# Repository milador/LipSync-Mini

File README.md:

# LipSync-Mini

Lipsync with updated electronics (Adafruit ItsyBitsy and RGB LED)

The LipSync is an assistive technology device developed by <a href="https://www.makersmakingchange.com/" download target="_blank">MakersMakingChange</a> (An initiative by the <a href="https://www.neilsquire.ca/" download target="_blank">Neil Squire Society</a>) which allows quadriplegics and other people with limited hand use the ability to use touchscreen mobile devices by manipulation of a mouth-operated joystick with integrated sip and puff controls. 

## Main LipSync github repository 

The LipSync Mini project is based on the <a href="https://github.com/makersmakingchange/LipSync" download target="_blank">LipSync</a>

## Changes Made

1. Dual color Led replaced by RGB addressable 
2. Arduino Micro replaced by Adafruit ItsyBitsy M0 (More memory and power)
3. Transistor and header pins for bluetooth module removed 
4. ItsyBitsy nRF52840 Express with bluetooth 5.0 is used for bluetooth version (Adafruit ItsyBitsy M0 replaced by ItsyBitsy nRF52840 Express)
5. Option to add ESP8266 Wifi Module to enable controlling IOT devices 
6. Option to add internal battery charger
7. Option to use internal input 3.5mm jack switch 
8. Option to replace sip and puff module with bite switch PCB

## License 

### MIT License

Copyright (c) 2020 Milador

Permission is hereby granted, free of charge, to any person obtaining a copy of this software and associated documentation files (the "Software"), to deal in the Software without restriction, including without limitation the rights to use, copy, modify, merge, publish, distribute, sublicense, and/or sell copies of the Software, and to permit persons to whom the Software is furnished to do so, subject to the following conditions:

The above copyright notice and this permission notice shall be included in all copies or substantial portions of the Software.

THE SOFTWARE IS PROVIDED "AS IS", WITHOUT WARRANTY OF ANY KIND, EXPRESS OR IMPLIED, INCLUDING BUT NOT LIMITED TO THE WARRANTIES OF MERCHANTABILITY, FITNESS FOR A PARTICULAR PURPOSE AND NONINFRINGEMENT. IN NO EVENT SHALL THE AUTHORS OR COPYRIGHT HOLDERS BE LIABLE FOR ANY CLAIM, DAMAGES OR OTHER LIABILITY, WHETHER IN AN ACTION OF CONTRACT, TORT OR OTHERWISE, ARISING FROM, OUT OF OR IN CONNECTION WITH THE SOFTWARE OR THE USE OR OTHER DEALINGS IN THE SOFTWARE.

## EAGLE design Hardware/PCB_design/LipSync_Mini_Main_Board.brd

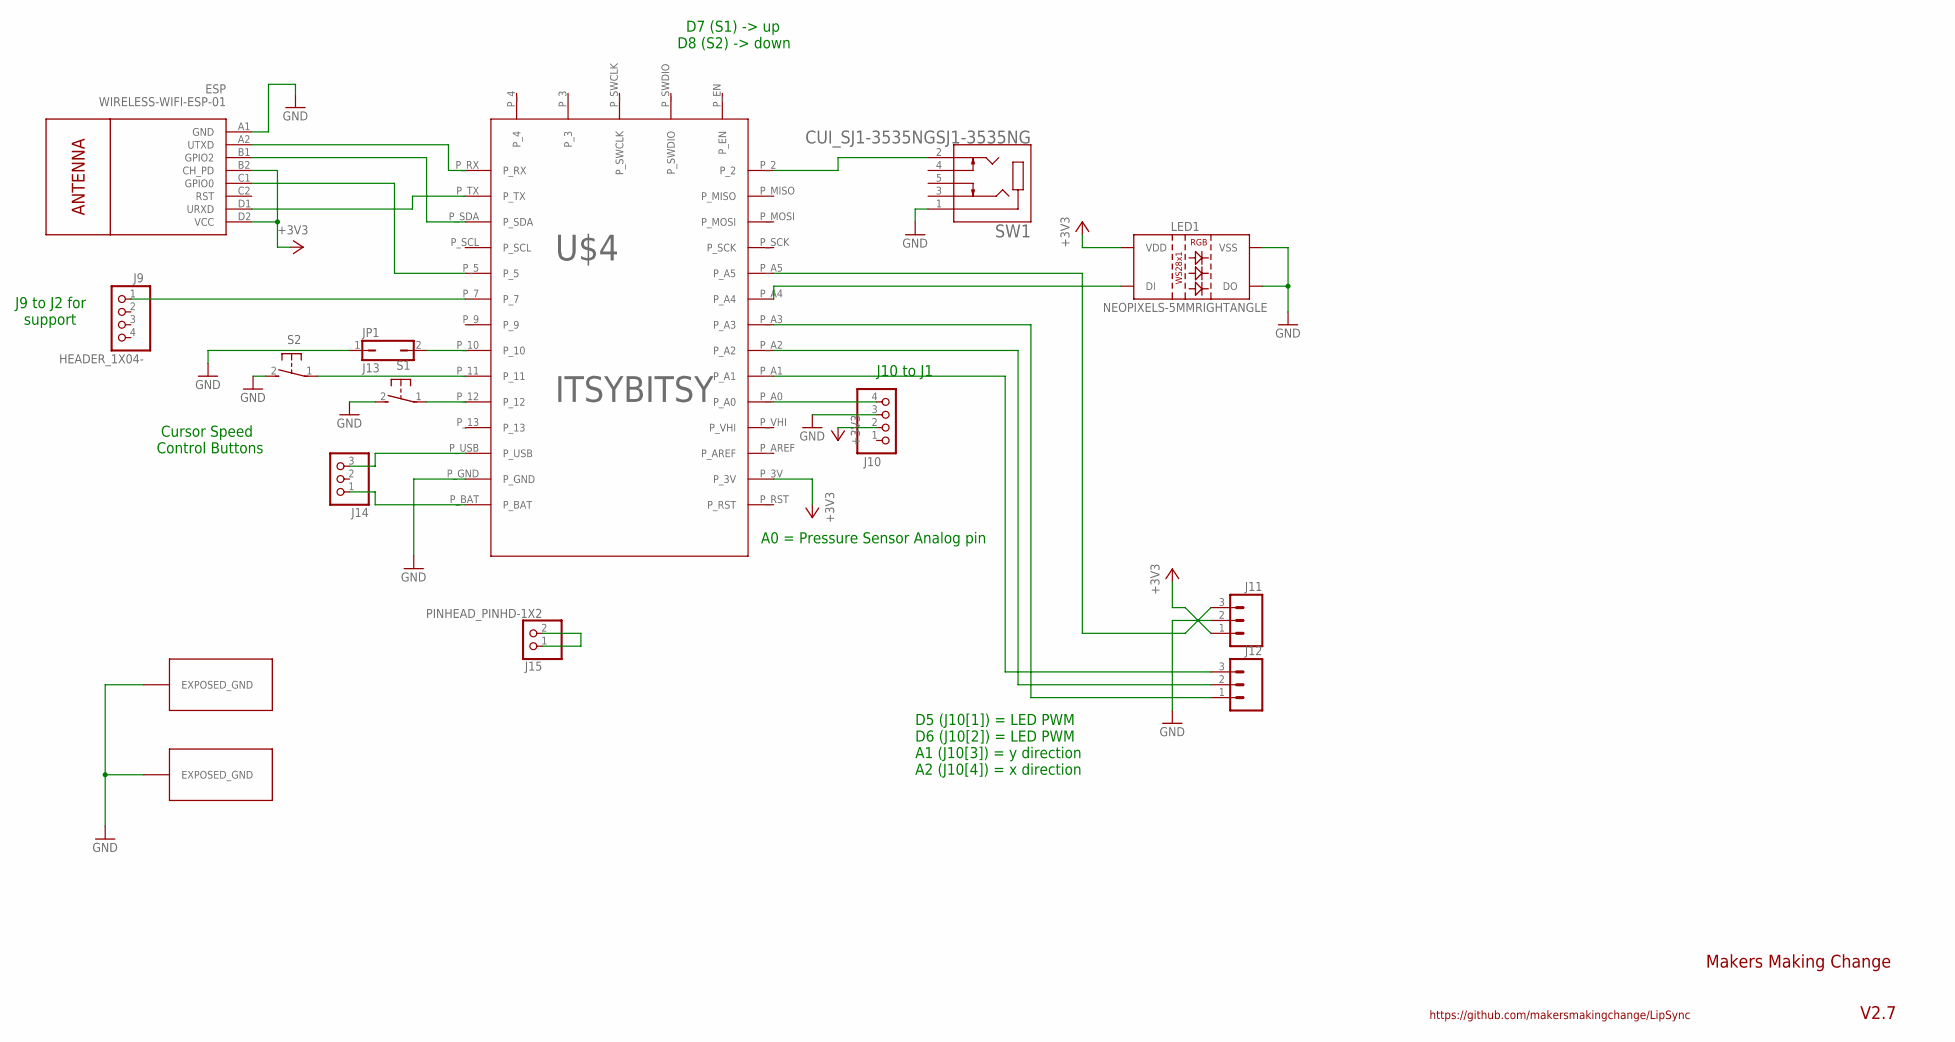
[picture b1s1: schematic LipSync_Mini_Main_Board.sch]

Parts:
ESP: WIRELESS-WIFI-ESP-01
J9, J10: HEADER_1X04-; 1X04
J11, J12: HEADER_1X03-/90; 1X03_LOCK/90
J13: JP1
J14: PINHEAD_PINHD-1X3; PINHEAD_1X03
J15: PINHEAD_PINHD-1X2; PINHEAD_1X02
LED1: NEOPIXELS-5MMRIGHTANGLE; NEOPIXELS-RIGHTANGLE-5MM
S1, S2: B3F_31-XXSKINNY; B3F-31XX-SKINNIER
SW1: CUI_SJ1-3535NGSJ1-3535NG; CUI_SJ1-3535NG
U$2, U$3: EXPOSED_GND
U$4: ITSYBITSY

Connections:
+3V3: ESP.B2 (CH_PD), ESP.D2 (VCC), J10.2, J11.1, LED1.P2 (VDD), U$4.P_3V
GND: ESP.A1 (GND), J10.3, J11.2, J13.1, LED1.P3 (VSS), LED1.P4 (DO), S1.2 (S), S2.2 (S), SW1.1, U$2.GND1, U$3.GND1, U$4.P_GND
unnamed: S1.1, U$4.P_12
unnamed: S2.1, U$4.P_11
unnamed: J13.2, U$4.P_10
unnamed: LED1.P1 (DI), U$4.P_A4
unnamed: J12.3, U$4.P_A1
unnamed: J12.2, U$4.P_A2
unnamed: ESP.D1 (URXD), U$4.P_TX
unnamed: ESP.A2 (UTXD), U$4.P_RX
unnamed: ESP.B1 (GPIO2), U$4.P_SDA
unnamed: J11.3, U$4.P_A5
unnamed: J10.4, U$4.P_A0
unnamed: J14.3, U$4.P_USB
unnamed: J14.1, U$4.P_BAT
unnamed: ESP.C1 (GPIO0), U$4.P_5
unnamed: SW1.2, U$4.P_2
unnamed: J12.1, U$4.P_A3
unnamed: J15.1, J15.2
unnamed: J9.1, U$4.P_7

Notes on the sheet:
J9 to J2 for support
D5 (J10[1]) = LED PWM D6 (J10[2]) = LED PWM A1 (J10[3]) = y direction A2 (J10[4]) = x direction
J10 to J1
Cursor Speed Control Buttons
D7 (S1) -> up D8 (S2) -> down
Makers Making Change
V2.7
https://github.com/makersmakingchange/LipSync
A0 = Pressure Sensor Analog pin

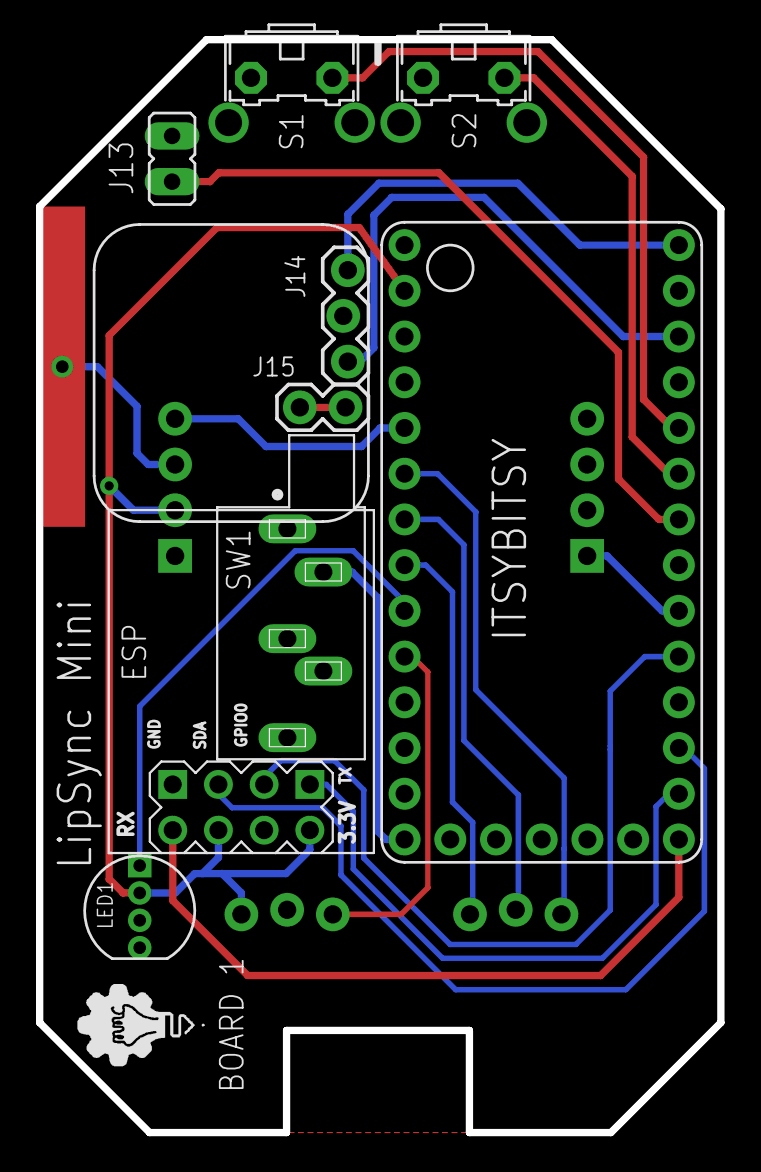
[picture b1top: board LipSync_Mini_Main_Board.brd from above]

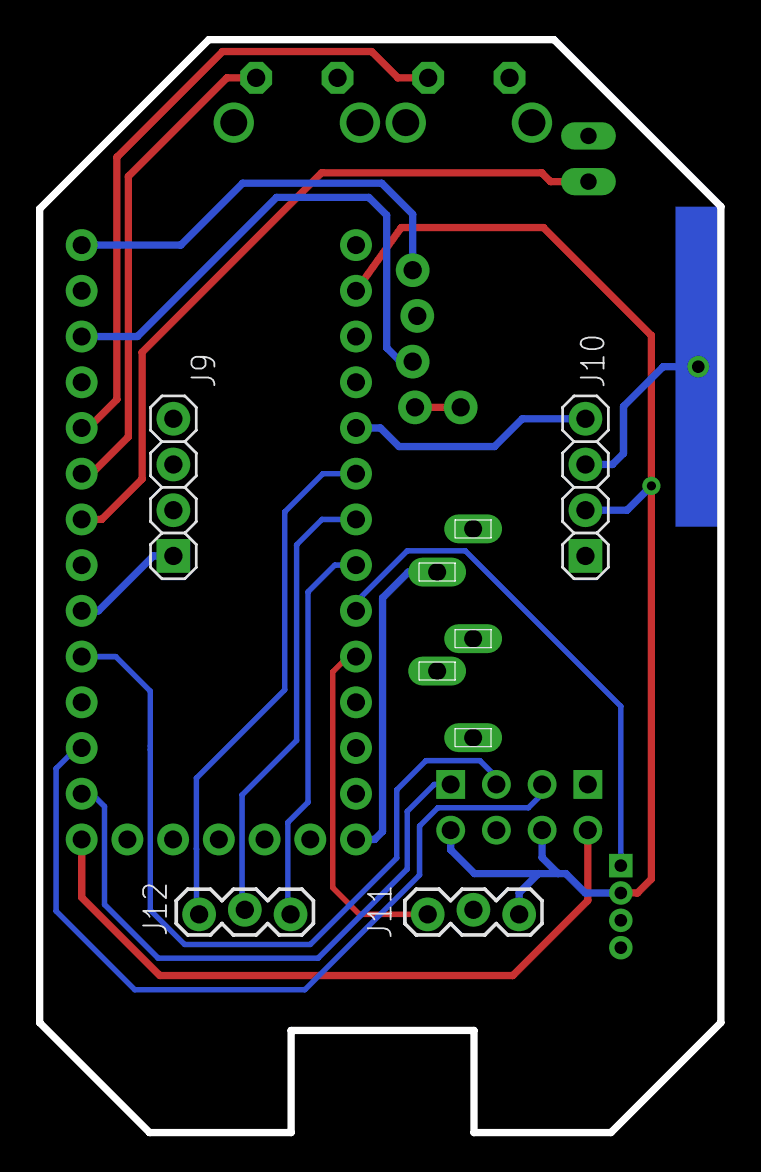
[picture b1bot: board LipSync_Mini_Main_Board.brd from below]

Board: 2 copper layers, 37.8 x 60.7 mm, 15 parts (5 on the bottom side), 20 nets.

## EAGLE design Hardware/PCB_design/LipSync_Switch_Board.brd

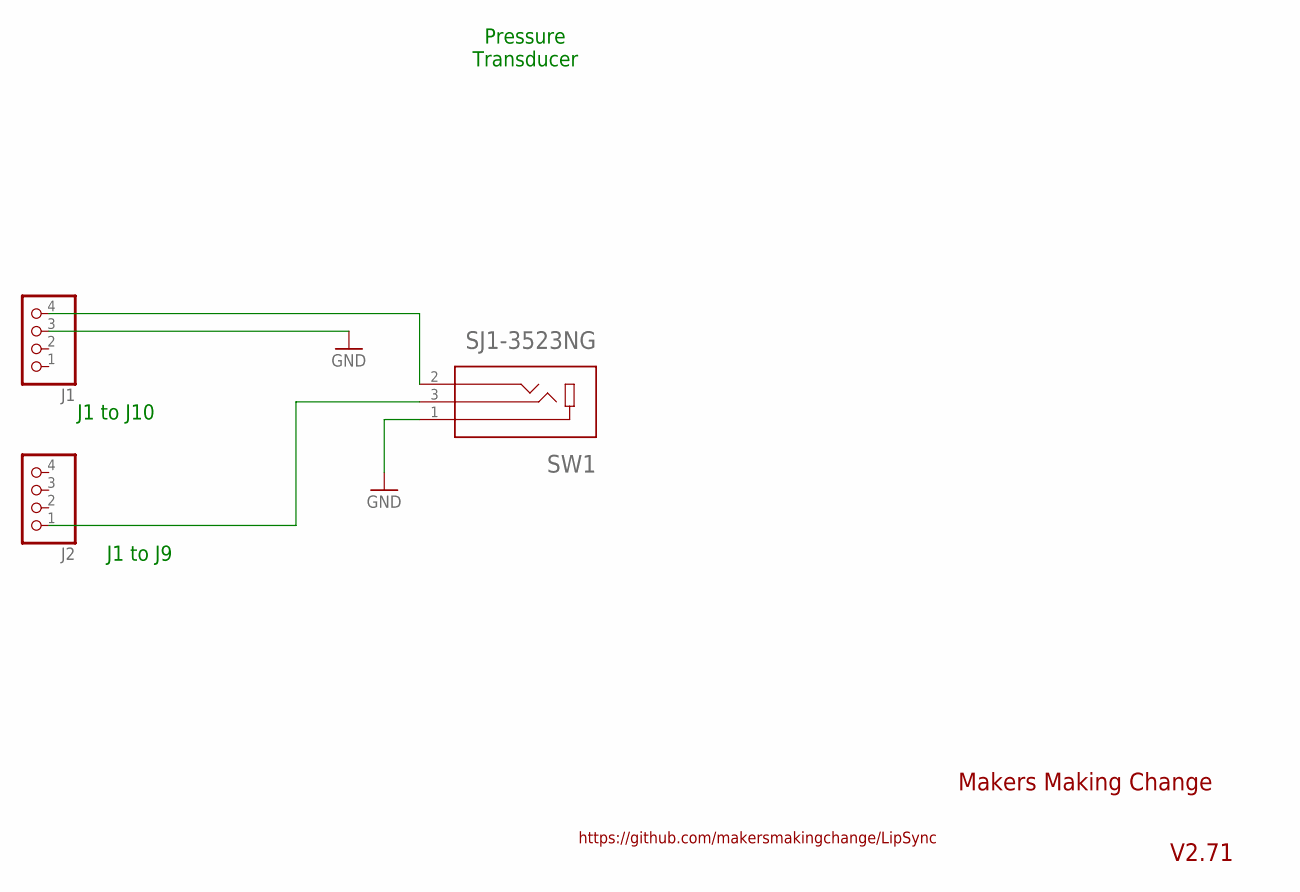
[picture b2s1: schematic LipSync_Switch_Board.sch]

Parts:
J1, J2: PINHEAD_PINHD-1X4; PINHEAD_1X04
SW1: SJ1-3523NG; CUI_SJ1-3523NG

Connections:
GND: J1.3, SW1.1
unnamed: J1.4, SW1.2
unnamed: J2.1, SW1.3

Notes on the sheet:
J1 to J10
Pressure Transducer
Makers Making Change
V2.71
https://github.com/makersmakingchange/LipSync
J1 to J9

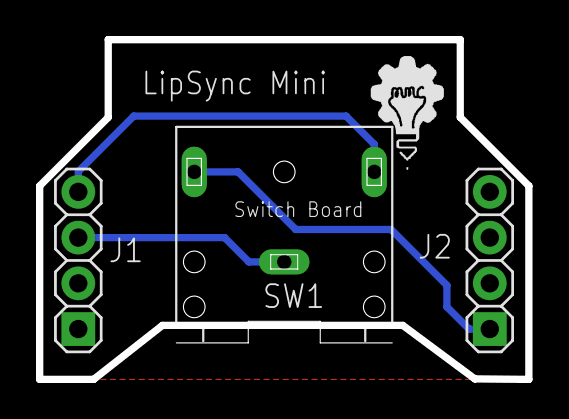
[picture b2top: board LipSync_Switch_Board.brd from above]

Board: 2 copper layers, 27.2 x 18.9 mm, 3 parts (0 on the bottom side), 3 nets.

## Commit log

2020-01-31 Updated PCB design with Itsybitsy board, RGB led, ESP IOT connection and ability to switch pressure sensor with bite switch board
2020-03-22 Added LipSync_Mini_Firmware USB code : Modified and tested sip and puff actions plus joystick movement Todo: Test Joystick move down again after fixing FSR Y Down
2020-03-22 Added part list for 3 versions
2020-03-22 Added enclosure 3D printing files
2020-03-22 Added sample picture
2020-03-22 Added readme file
    Added the changes made
2020-03-22 Updated part list for wifi version
2020-03-22 Updated readme file
    Updated readme file
2021-02-26 Create LICENSE

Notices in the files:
parts and their libraries:
SparkFun-Aesthetics: Licensing: Creative Commons ShareAlike 4.0 International - https://creativecommons.org/licenses/by-sa/4.0
